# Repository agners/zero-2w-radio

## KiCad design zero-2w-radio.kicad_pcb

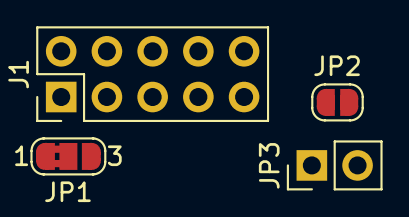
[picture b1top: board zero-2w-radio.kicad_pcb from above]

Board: 2 copper layers, 4 parts (0 on the bottom side), 5 nets, no tracks yet.

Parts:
J1: Raspberry_Pi_2_3; PinHeader_2x05_P2.54mm_Vertical
JP1: SolderJumper_3_Bridged12; SolderJumper-3_P1.3mm_Bridged2Bar12_RoundedPad1.0x1.5mm_Num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
JP2: SolderJumper_2_Open; SolderJumper-2_P1.3mm_Open_RoundedPad1.0x1.5mm
JP3: Jumper_2_Bridged; PinHeader_1x02_P2.54mm_Vertical

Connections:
+3V3: J1.1 (3V3), JP1.3 (B)
+5V: J1.2 (5V), J1.4 (5V), JP1.2 (C)
GND: J1.6 (GND), J1.9 (GND)
unnamed: JP1.1 (A), JP2.1 (A), JP3.1 (A)
VDD: JP2.2 (B), JP3.2 (B)

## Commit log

2024-03-22 Updated some footprints
